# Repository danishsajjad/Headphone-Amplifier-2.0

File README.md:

# Headphone-Amplifier-2.0
 Attempt to create a headphone amplifier.

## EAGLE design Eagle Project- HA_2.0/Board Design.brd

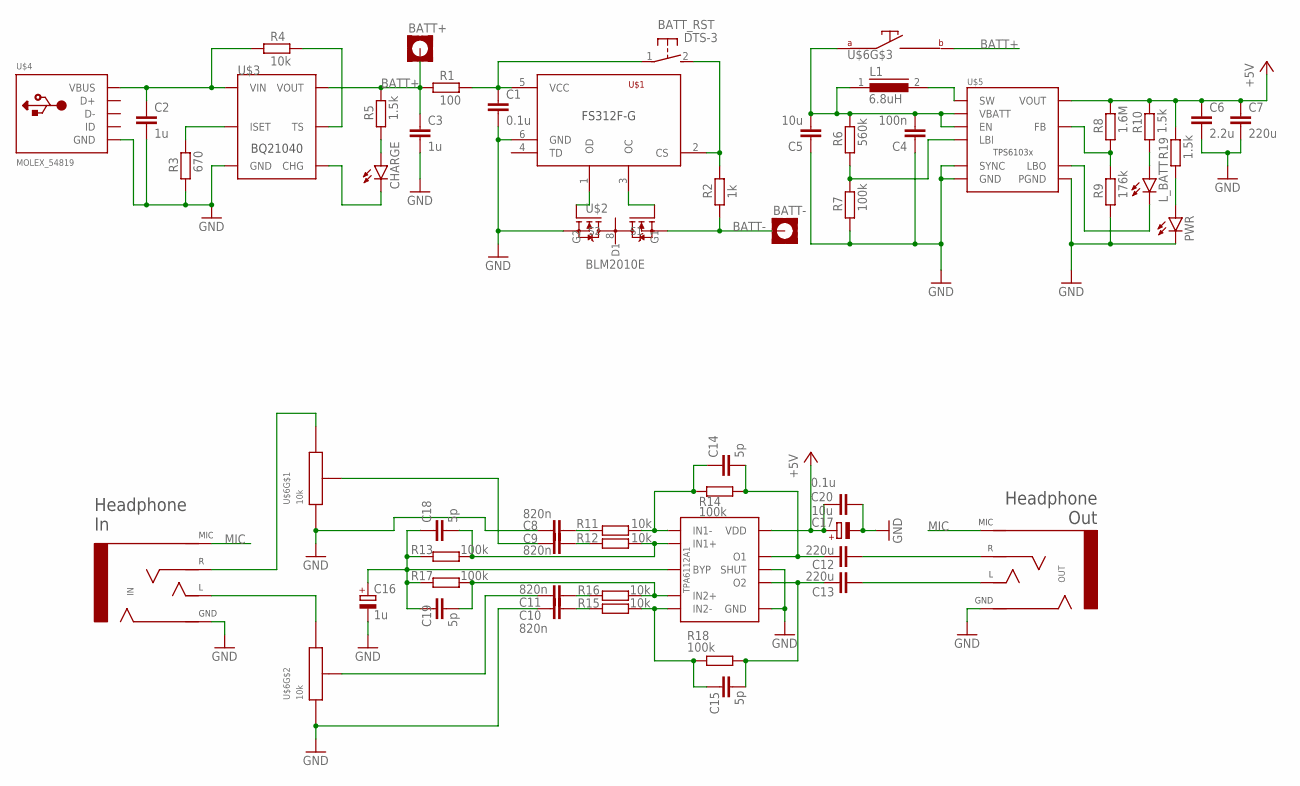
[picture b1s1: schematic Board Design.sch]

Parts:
BATT+: MOUNT-PAD-SQUARE2.8; 2,8-PAD-SQUARE
BATT-: MOUNT-PAD-SQUARE2.8; 2,8-PAD-SQUARE
BATT_RST: DTS-3
C1, C20: 0.1u; C1206
C2, C3: 1u; C1206
C4: 100n; C1206
C5: 10u; C1206
C6: 2.2u; C1206
C7: 220u; C1206
C8, C9, C10, C11: 820n; C1812
C12, C13: 220u; C1210
C14, C15, C18, C19: 5p; C1206
C16: 1u; PANASONIC_B
C17: 10u; PANASONIC_B
CHARGE: LEDSMT1206; 1206
IN: PJ-35372
L1: 6.8uH; DR127
L_BATT: LEDSMT1206; 1206
OUT: PJ-35372
PWR: LEDSMT1206; 1206
R1: 100; M1206
R2: 1k; M1206
R3: 670; M1206
R4: 10k; M1206
R5, R10, R19: 1.5k; M1206
R6: 560k; M1206
R7: 100k; M1206
R8: 1.6M; M1206
R9: 176k; M1206
R11, R12, R15, R16: 10k; 0204V
R13, R14, R17, R18: 100k; 0204V
TPA6112A1: TPA6112A2; MSOP-10
U$1: FS312F-G; SOT23-6
U$2: BLM2010E; TSSOP8
U$3: BQ21040M; SOT23-6
U$4: MOLEX_54819
U$5: TPS61032; TSSOP16L
U$6: 10k; RK097-DUAL-ELEMENT-W/SWITCH

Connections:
+5V: C6.1, C7.1, C17.+, C20.1, R8.2, R10.2, R19.2, TPA6112A1.10 (VDD), U$5.13 (VOUT), U$5.14 (VOUT), U$5.15 (VOUT)
BATT+: BATT+.B2,8, C3.1, R1.1, R5.2, U$3.2 (VOUT), U$6.S2
BATT-: BATT-.B2,8, R2.1, U$2.2 (S1), U$2.3 (S1)
GND: C1.2, C2.2, C3.2, C4.1, C5.1, C6.2, C7.2, C8.1, C10.1, C16.-, C17.-, C20.2, IN.2 (R2), IN.6 (R2), OUT.2 (R2), OUT.6 (R2), PWR.C, R3.1, R7.1, R9.1, TPA6112A1.5 (GND), TPA6112A1.6 (SHUT), U$1.6 (GND), U$2.6 (S2), U$2.7 (S2), U$3.5 (GND), U$4.GND, U$5.3 (PGND), U$5.4 (PGND), U$5.5 (PGND), U$5.8 (SYNC), U$5.11 (GND), U$6.1-1 (1), U$6.2-1 (1)
MIC: IN.1 (S), IN.5 (S), OUT.1 (S), OUT.5 (S)
MNVMNV: C4.2, C5.2, L1.1, R6.2, U$5.6 (VBATT), U$5.9 (EN), U$6.S1
unnamed: C2.1, R4.1, U$3.4 (VIN), U$4.VBUS
unnamed: BATT_RST.1, C1.1, R1.2, U$1.5 (VCC)
unnamed: U$1.3 (OC), U$2.4 (G1)
unnamed: U$1.1 (OD), U$2.5 (G2)
unnamed: R3.2, U$3.6 (ISET)
unnamed: BATT_RST.2, R2.2, U$1.2 (CS)
unnamed: R4.2, U$3.1 (TS)
unnamed: CHARGE.A, R5.1
unnamed: CHARGE.C, U$3.3 (CHG)
unnamed: L1.2, U$5.1 (SW), U$5.2 (SW)
unnamed: L_BATT.C, U$5.10 (LBO)
unnamed: L_BATT.A, R10.1
unnamed: C16.+, C18.1, C19.1, R13.1, R17.1, TPA6112A1.4 (BYP)
unnamed: R8.1, R9.2, U$5.12 (FB)
unnamed: PWR.A, R19.1
unnamed: C12.1, C14.2, R14.2, TPA6112A1.1 (O1)
unnamed: R6.1, R7.2, U$5.7 (LBI)
unnamed: C13.1, C15.2, R18.2, TPA6112A1.9 (O2)
unnamed: C8.2, R11.1
unnamed: C9.2, R12.1
unnamed: C18.2, R12.2, R13.2, TPA6112A1.3 (IN1+)
unnamed: C14.1, R11.2, R14.1, TPA6112A1.2 (IN1-)
unnamed: C11.1, U$6.2-3 (3)
unnamed: C19.2, R16.2, R17.2, TPA6112A1.7 (IN2+)
unnamed: C11.2, R16.1
unnamed: C10.2, R15.1
unnamed: C15.1, R15.2, R18.1, TPA6112A1.8 (IN2-)
unnamed: C9.1, U$6.1-3 (3)
unnamed: IN.4 (T), IN.8 (T), U$6.2-2 (2)
unnamed: IN.3 (R1), IN.7 (R1), U$6.1-2 (2)
unnamed: C13.2, OUT.4 (T), OUT.8 (T)
unnamed: C12.2, OUT.3 (R1), OUT.7 (R1)

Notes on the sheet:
Headphone In
Headphone Out

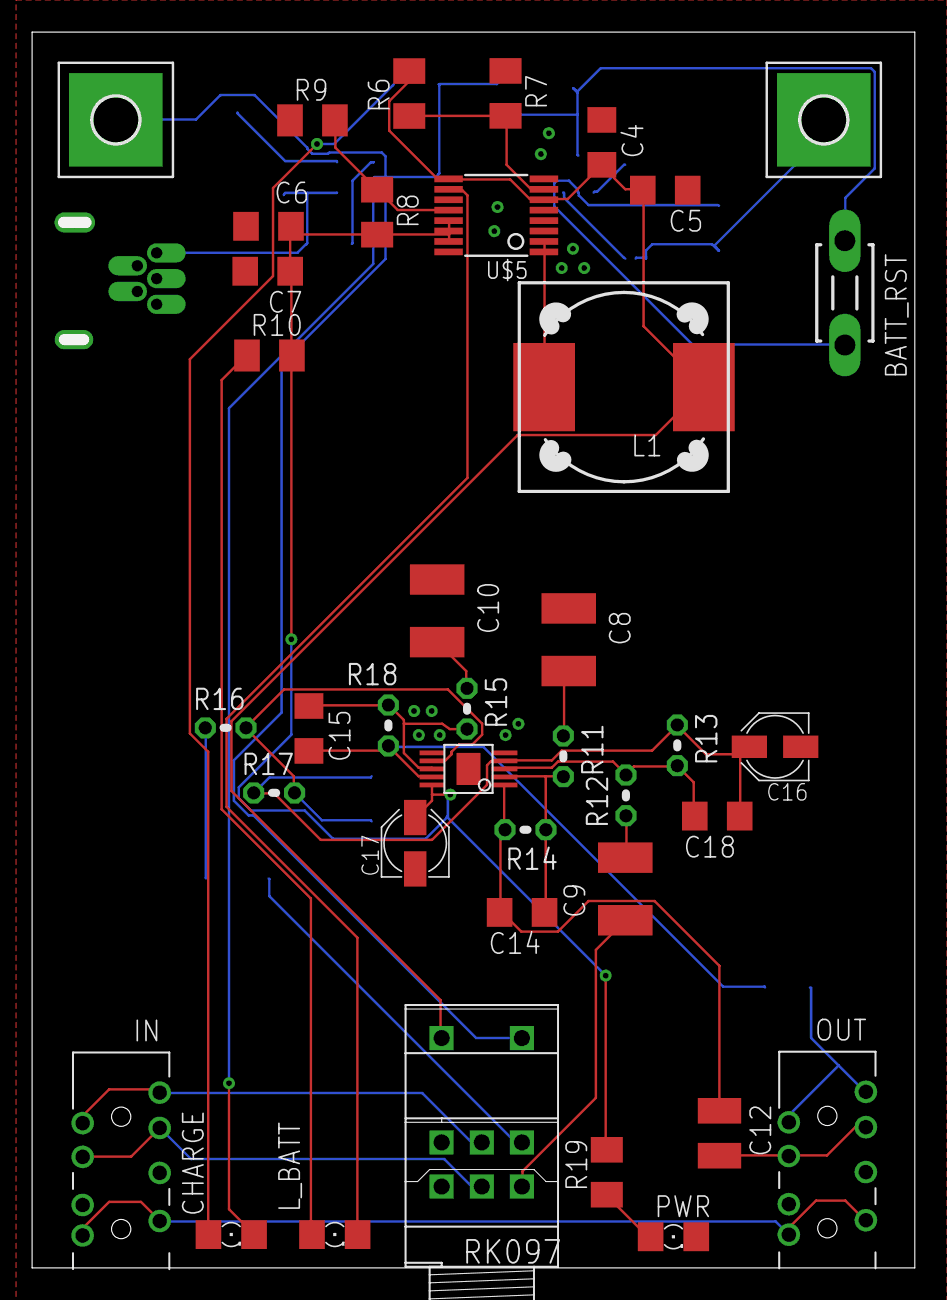
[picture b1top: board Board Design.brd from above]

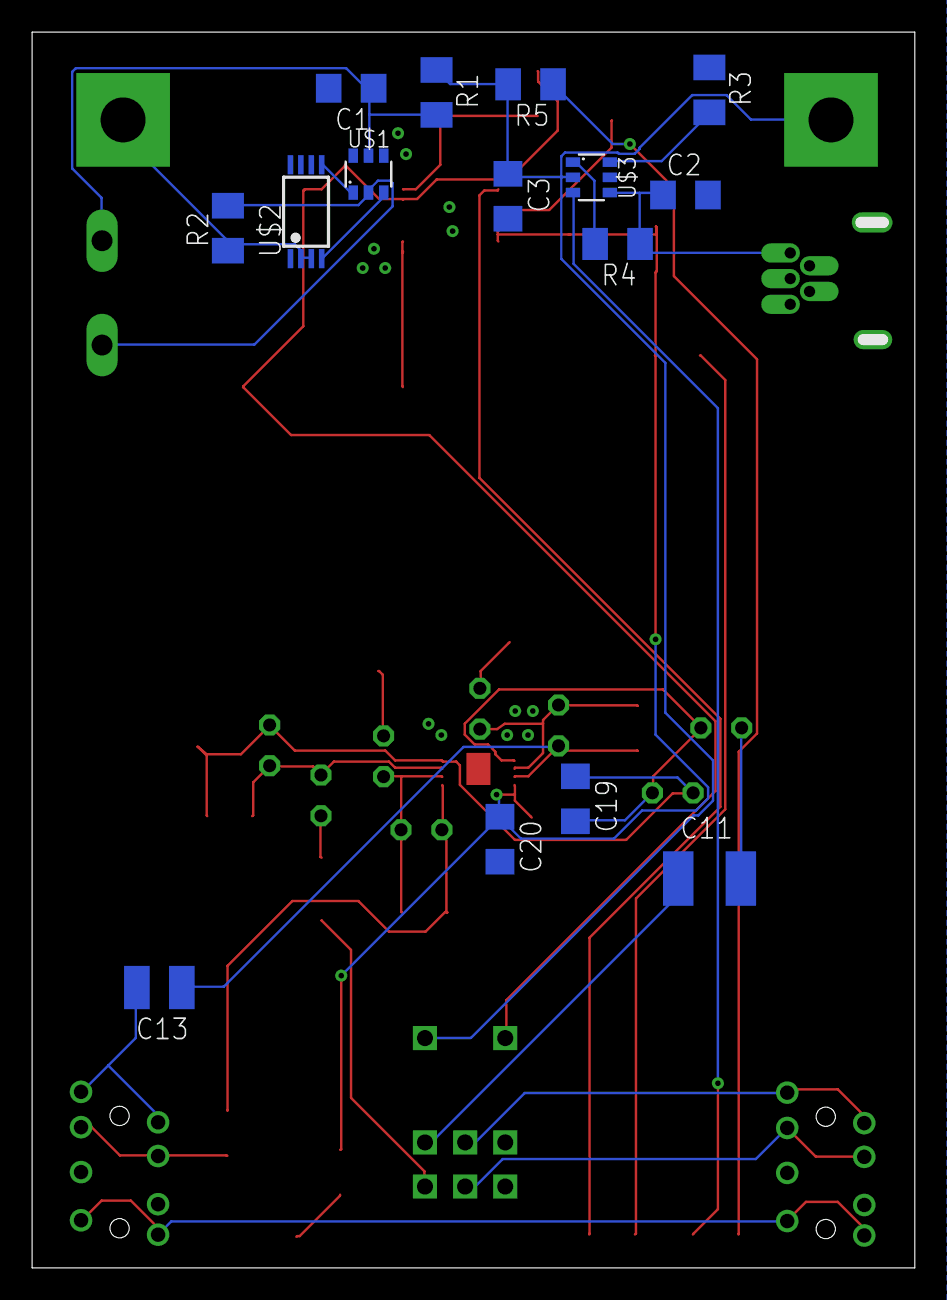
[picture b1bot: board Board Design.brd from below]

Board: 2 copper layers, 54.3 x 76.3 mm, 55 parts (15 on the bottom side), 38 nets.

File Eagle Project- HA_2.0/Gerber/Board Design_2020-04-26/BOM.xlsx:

Qty | Device | Value | Package | Parts | Description
15 | LED |  | 1206 | CHARGE, L_BATT, PWR | LED
5 | ARG06DTC1000 | 100 | 1206 | R1 | RESISTOR
5 | AR06DTCV1001 | 1k | 1206 | R2 | RESISTOR
5 | AR06FTCV6800 | 680 | 1206 | R3 | RESISTOR
5 | AR06DTDV1002 | 10k | 1206 | R4 | RESISTOR
5 | TR1206D176KP0550 | 176k | 1206 | R9 | RESISTOR
15 | ARG06DTC1501 | 1.5k | 1206 | R5, R10, R19 | RESISTOR
5 | ARG06FTC1604 | 1.60M | 1206 | R8 | RESISTOR
20 | RNU18F1003A520NH | 100k |  | R13, R14, R17, R18 | RESISTOR
5 | AR06DTDV1003 | 100k | 1206 | R7 | RESISTOR
5 | TR1206D560KP0525Z | 560k | 1206 | R6 | RESISTOR
20 | RNU18F1002A520NH | 10k |  | R11, R12, R15, R16 | RESISTOR
5 | TMK316BJ106ML-T | 10u | 1206 | C5 | Ceramic/Tentalum Capacitor
5 | EEEHB1H1R0R | 1u | PANASONIC_B | C16 | Aluminium Electrolytic
5 | EEEHD1V100AR | 10u | PANASONIC_B | C17 | Aluminium Electrolytic
5 | CL31B104KBCNNNC | 100n | 1206 | C4 | Ceramic Capacitor
10 | CL31B105KAHNNNE | 1u | 1206 | C2, C3 | Ceramic
10 | CL31B104KBCNNNC | 0.1u | 1206 | C1, C20 | Ceramic
5 | CL31B225KBHNNNE | 2.2u | 1206 | C6 | Ceramic
5 | 2R5TPE220MAZB | 220u | 1206 | C7 | Tentalum
10 | 2R5TPE220MAZB | 220u | 1210 | C12, C13 | Low ESR Ceramic
20 | TCC1206COG5R0D500DT | 5p | 1206 | C14, C15, C18, C19 | Ceramic
20 | C1812X824K101T | 820n | 1812 | C8, C9, C10, C11 | LOW ESR Ceramic
5 | MS1350-6R8M | 6.8uH | SMD | L1 | High Power Density, High Efficiency, Shielded Inductors
5 | RK0971221Z05 | 10k | Through Hole | U$6 | Alps RK097 Dual Pot with Switch Part.
10 | PJ-35372 | PJ-35372 | PJ-35372 | IN, OUT | Headphone Jack
5 | 54819-0519 | MOLEX_54819 | Through Hole | U$4 | USB Power Connector
5 | BLM2012E |  | TSSOP8 | U$2
5 | BQ21040DBVR |  | SOT23-6 | U$3
5 | DTS-32K-V-B |  | Through Hole | BATT_RST | SPST Tactile Switch
5 | FS312F-G |  | SOT23-6 | U$1 | Battery Protection IC
5 | TPA6112A2DGQR |  | MSOP-10 | TPA6112A1 | Amplifier IC
5 | TPS61032PWPR |  | TSSOP16L | U$5 | Boost Converter
